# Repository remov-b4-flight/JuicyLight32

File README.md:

# JuicyLight32
USB color light embeded project.

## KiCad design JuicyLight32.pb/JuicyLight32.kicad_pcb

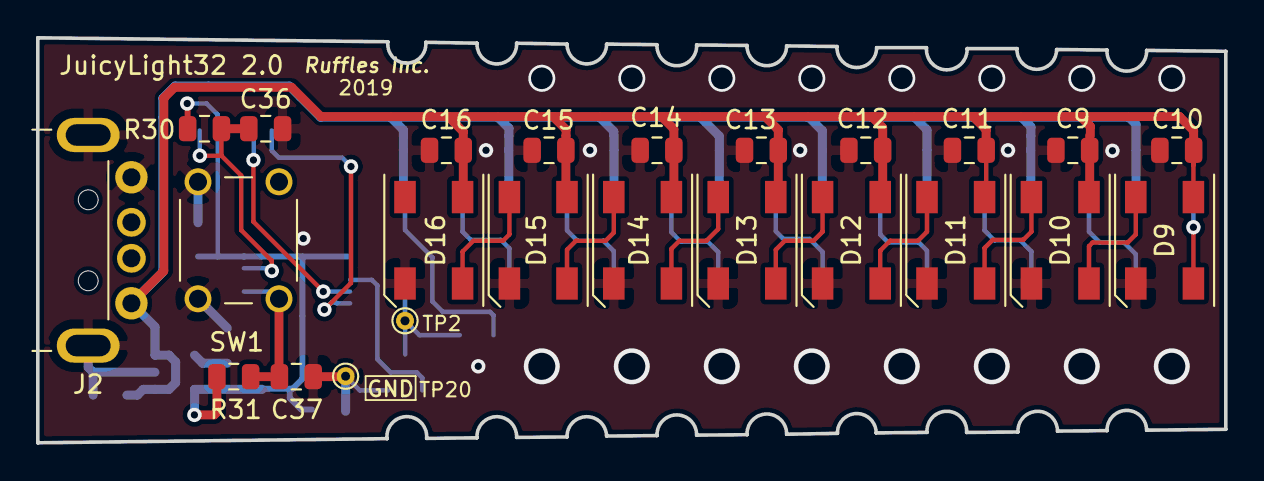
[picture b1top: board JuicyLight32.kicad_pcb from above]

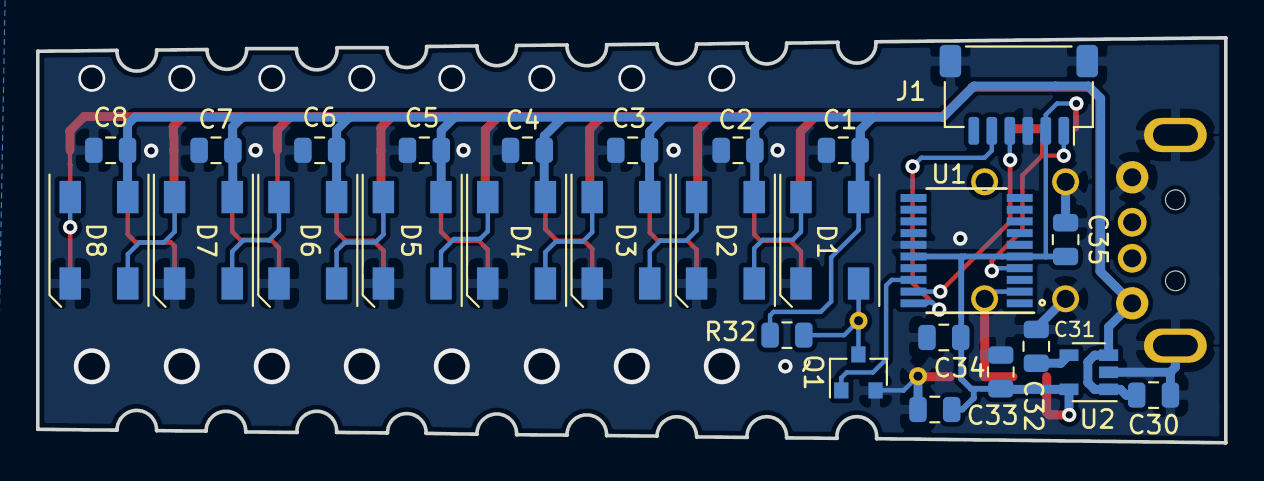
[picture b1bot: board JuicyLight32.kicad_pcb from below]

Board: 2 copper layers, 66.0 x 22.5 mm, 51 parts (27 on the bottom side), 25 nets.

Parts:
C1, C2, C3, C4, C5, C6, C7, C8, C9, C10, C11, C12, C13, C14, C15, C16, C33, C35: 0.1u; C_0805_2012Metric
C30, C32, C36, C37: 1u; C_0805_2012Metric
C31: 0.01u; C_0805_2012Metric
C34: 10u; C_0805_2012Metric
D1, D2, D3, D4, D5, D6, D7, D8, D9, D10, D11, D12, D13, D14, D15, D16: WS2812B; OST45050C1A
J1: SM06B; JST_SH_SM06B-SRSS-TB_1x06-1MP_P1.00mm_Horizontal
J2: USB_A; USB_A_TH
Q1: BSS138; SOT-23
R30, R31: 10K; R_0805_2012Metric
R32: 4.7K; R_0805_2012Metric
SW1: SW_Push; SW_TACT_6mm
TP2: D1IN33; TestPoint_THTPad_D1.0mm_Drill0.5mm
TP20: GND; TestPoint_THTPad_D1.0mm_Drill0.5mm
U1: STM32F042F6Px; TSSOP-20_4.4x6.5mm_P0.65mm
U2: NJM2896F33; SOT-23-5

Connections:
+3V3: C32.1, C33.1, C34.1, C35.1, J1.2, R30.1, R31.1, U1.5, U1.16, U2.5
+5V: C1.1, C2.1, C3.1, C4.1, C5.1, C6.1, C7.1, C8.1, C9.1, C10.1, C11.1, C12.1, C13.1, C14.1, C15.1, C16.1, C30.1, D1.1, D2.1, D3.1, D4.1, D5.1, D6.1, D7.1, D8.1, D9.1, D10.1, D11.1, D12.1, D13.1, D14.1, D15.1, D16.1, J2.1, R32.1, U2.1, U2.3
/D1IN: D1.4, Q1.3, R32.2, TP2.1
/D1OUT: D1.2, D2.4
/D2OUT: D2.2, D3.4
/D3OUT: D3.2, D4.4
/D4OUT: D4.2, D5.4
/D5OUT: D5.2, D6.4
/D6OUT: D6.2, D7.4
/D7OUT: D7.2, D8.4
/D8OUT: D8.2, D9.4
/D9OUT: D9.2, D10.4
/D10OUT: D10.2, D11.4
/D11OUT: D11.2, D12.4
/D12OUT: D12.2, D13.4
/D13OUT: D13.2, D14.4
/D14OUT: D14.2, D15.4
/D15OUT: D15.2, D16.4
/LEDOUT: Q1.1, U1.18
/MOD_SW: C37.1, R31.2, SW1.2, U1.2
/NRST: C36.1, J1.1, R30.2, U1.4
/SWCLK: J1.5, U1.20
/SWDIO: J1.4, U1.19
GND: C1.2, C2.2, C3.2, C4.2, C5.2, C6.2, C7.2, C8.2, C9.2, C10.2, C11.2, C12.2, C13.2, C14.2, C15.2, C16.2, C30.2, C31.2, C32.2, C33.2, C34.2, C35.2, C36.2, C37.2, D1.3, D2.3, D3.3, D4.3, D5.3, D6.3, D7.3, D8.3, D9.3, D10.3, D11.3, D12.3, D13.3, D14.3, D15.3, D16.3, J1.3, J1.MP, J2.4, J2.5, Q1.2, SW1.1, TP20.1, U1.15, U2.2
unnamed: C31.1, U2.4

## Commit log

2019-05-03 Initial commit
    Long press implemented
2019-05-03 edit README.md
2019-05-05 Improve double push function.
    Add 'at RAINBOW mode, return to STATIC by sigle push.'
2019-05-28 Add pattern 'DD' in dynamic mode.
2019-05-29 Move to STM32CubeIDE & Reduce LEDPulse[] with uint16_t to uint8_t
2019-06-11 R2.0
    Board Revision 2.0
2019-06-17 Adjust double push detetion & moved to STM32Cube 1.0.1
2019-06-27 Fit with board Revision 2.0
2019-06-29 Pink color adjustment
2020-04-28 Yellow color adjustment for through tracing paper.
2022-04-20 Added 'rotational' pattern at dynamic mode
2022-04-21 modify rotation pattern
